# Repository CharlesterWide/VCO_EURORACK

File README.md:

# VCO_EURORACK
Saw core VCO for eurack

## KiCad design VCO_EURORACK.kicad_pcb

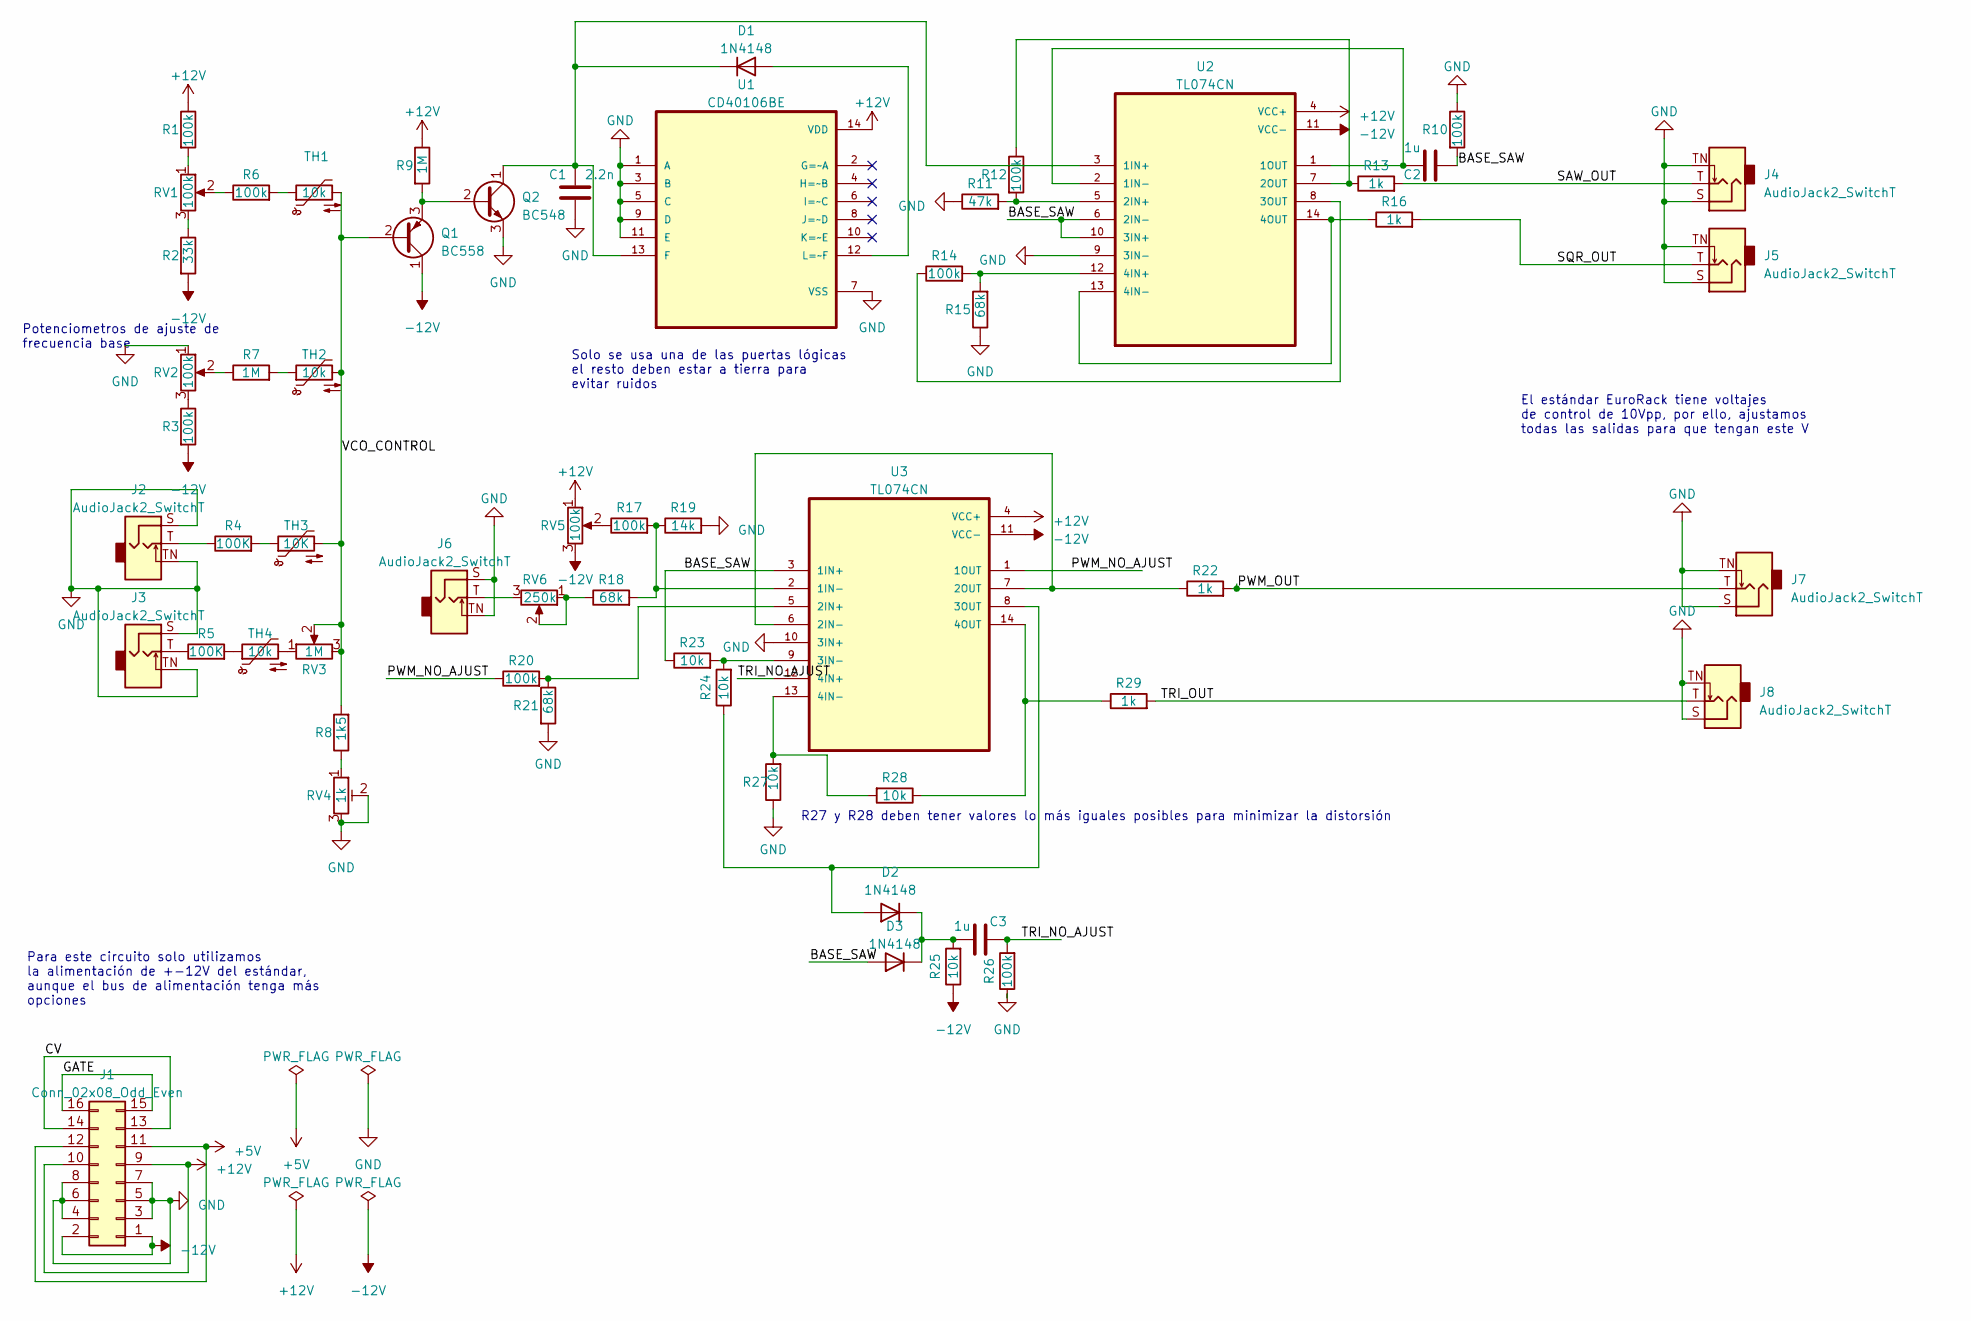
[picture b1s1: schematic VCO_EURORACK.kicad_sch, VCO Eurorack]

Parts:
C1: 2.2n; C_1206_3216Metric_Pad1.33x1.80mm_HandSolder
C2, C3: 1u; C_1206_3216Metric_Pad1.33x1.80mm_HandSolder
D1, D2, D3: 1N4148; D_DO-35_SOD27_P7.62mm_Horizontal
J1: Conn_02x08_Odd_Even; IDC-Header_2x08_P2.54mm_Vertical
J2, J3, J4, J5, J6, J7, J8: AudioJack2_SwitchT; Jack_3.5mm_QingPu_WQP-PJ398SM_Vertical_CircularHoles
Q1: BC558; TO-92_Inline
Q2: BC548; TO-92_Inline
R1, R3, R6, R10, R12, R14, R17, R20, R26: 100k; R_1206_3216Metric_Pad1.30x1.75mm_HandSolder
R2: 33k; R_1206_3216Metric_Pad1.30x1.75mm_HandSolder
R4, R5: 100K; R_1206_3216Metric_Pad1.30x1.75mm_HandSolder
R7, R9: 1M; R_1206_3216Metric_Pad1.30x1.75mm_HandSolder
R8: 1k5; R_1206_3216Metric_Pad1.30x1.75mm_HandSolder
R11: 47k; R_1206_3216Metric_Pad1.30x1.75mm_HandSolder
R13, R16, R22, R29: 1k; R_1206_3216Metric_Pad1.30x1.75mm_HandSolder
R15, R18, R21: 68k; R_1206_3216Metric_Pad1.30x1.75mm_HandSolder
R19: 14k; R_1206_3216Metric_Pad1.30x1.75mm_HandSolder
R23, R24, R25, R27, R28: 10k; R_1206_3216Metric_Pad1.30x1.75mm_HandSolder
RV1, RV2, RV5: 100k; Potentiometer_Omeg_PC16BU_Vertical
RV3: 1M; Potentiometer_Omeg_PC16BU_Vertical
RV4: 1k; Potentiometer_Bourns_3296Y_Vertical
RV6: 250k; Potentiometer_Omeg_PC16BU_Vertical
TH1, TH2, TH4: 10k; R_1206_3216Metric_Pad1.30x1.75mm_HandSolder
TH3: 10K; R_1206_3216Metric_Pad1.30x1.75mm_HandSolder
U1: CD40106BE; DIP794W45P254L1969H508Q14
U2, U3: TL074CN; DIP794W45P254L1969H508Q14

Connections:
+5V: J1.11, J1.12
+12V: J1.9, J1.10, R1.1, R9.1, RV5.1, U1.14 (VDD), U2.4 (VCC+), U3.4 (VCC+)
-12V: J1.1, J1.2, Q1.1 (C), R2.2, R3.2, R25.1, RV5.3, U2.11 (VCC-), U3.11 (VCC-)
/BASE_SAW: C2.2, D3.2 (A), R10.2, R23.1, U2.6 (2IN-), U2.10 (3IN+), U3.3 (1IN+)
/CV: J1.13, J1.14
/GATE: J1.15, J1.16
/PWM_NO_AJUST: R20.1, U3.1 (1OUT)
/PWM_OUT: J7.T, R22.2
/SAW_OUT: J4.T, R13.2
/SQR_OUT: J5.T, R16.2
/TRI_NO_AJUST: C3.2, R26.2, U3.12 (4IN+)
/TRI_OUT: J8.T, R29.2
/VCO_CONTROL: Q1.2 (B), R8.2, RV3.2, RV3.3, TH1.2, TH2.2, TH3.2
GND: C1.2, J1.3, J1.4, J1.5, J1.6, J1.7, J1.8, J2.S, J2.TN, J3.S, J3.TN, J4.S, J4.TN, J5.S, J5.TN, J6.S, J6.TN, J7.S, J7.TN, J8.S, J8.TN, Q2.3 (E), R10.1, R11.1, R15.1, R19.2, R21.2, R26.1, R27.1, RV2.1, RV4.2, RV4.3, U1.1 (A), U1.3 (B), U1.5 (C), U1.7 (VSS), U1.9 (D), U1.11 (E), U2.9 (3IN-), U3.10 (3IN+)
unnamed: D1.2 (A), U1.12 (L=~F)
unnamed: C1.1, D1.1 (K), Q2.1 (C), U1.13 (F), U2.3 (1IN+)
unnamed: D2.2 (A), R24.1, U3.8 (3OUT)
unnamed: C3.1, D2.1 (K), D3.1 (K), R25.2
unnamed: J2.T, R4.1
unnamed: J3.T, R5.1
unnamed: J6.T, RV6.3
unnamed: Q1.3 (E), Q2.2 (B), R9.2
unnamed: R1.2, RV1.1
unnamed: R2.1, RV1.3
unnamed: R3.1, RV2.3
unnamed: R4.2, TH3.1
unnamed: R5.2, TH4.1
unnamed: R6.1, RV1.2
unnamed: R6.2, TH1.1
unnamed: R7.1, RV2.2
unnamed: R7.2, TH2.1
unnamed: R8.1, RV4.1
unnamed: R17.1, RV5.2
unnamed: R18.1, RV6.1, RV6.2
unnamed: RV3.1, TH4.2
unnamed: C2.1, U2.1 (1OUT), U2.2 (1IN-)
unnamed: R11.2, R12.2, U2.5 (2IN+)
unnamed: R12.1, R13.1, U2.7 (2OUT)
unnamed: R14.1, U2.8 (3OUT)
unnamed: R14.2, R15.2, U2.12 (4IN+)
unnamed: R16.1, U2.13 (4IN-), U2.14 (4OUT)
unnamed: R17.2, R18.2, R19.1, U3.2 (1IN-)
unnamed: R20.2, R21.1, U3.5 (2IN+)
unnamed: R22.1, U3.6 (2IN-), U3.7 (2OUT)
unnamed: R23.2, R24.2, U3.9 (3IN-)
unnamed: R27.2, R28.2, U3.13 (4IN-)
unnamed: R28.1, R29.1, U3.14 (4OUT)

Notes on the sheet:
Para este circuito solo utilizamos la alimentación de +-12V del estándar, aunque el bus de alimentación tenga más opciones
R27 y R28 deben tener valores lo más iguales posibles para minimizar la distorsión
El estándar EuroRack tiene voltajes de control de 10Vpp, por ello, ajustamos todas las salidas para que tengan este V
Potenciometros de ajuste de frecuencia base
Solo se usa una de las puertas lógicas el resto deben estar a tierra para evitar ruidos

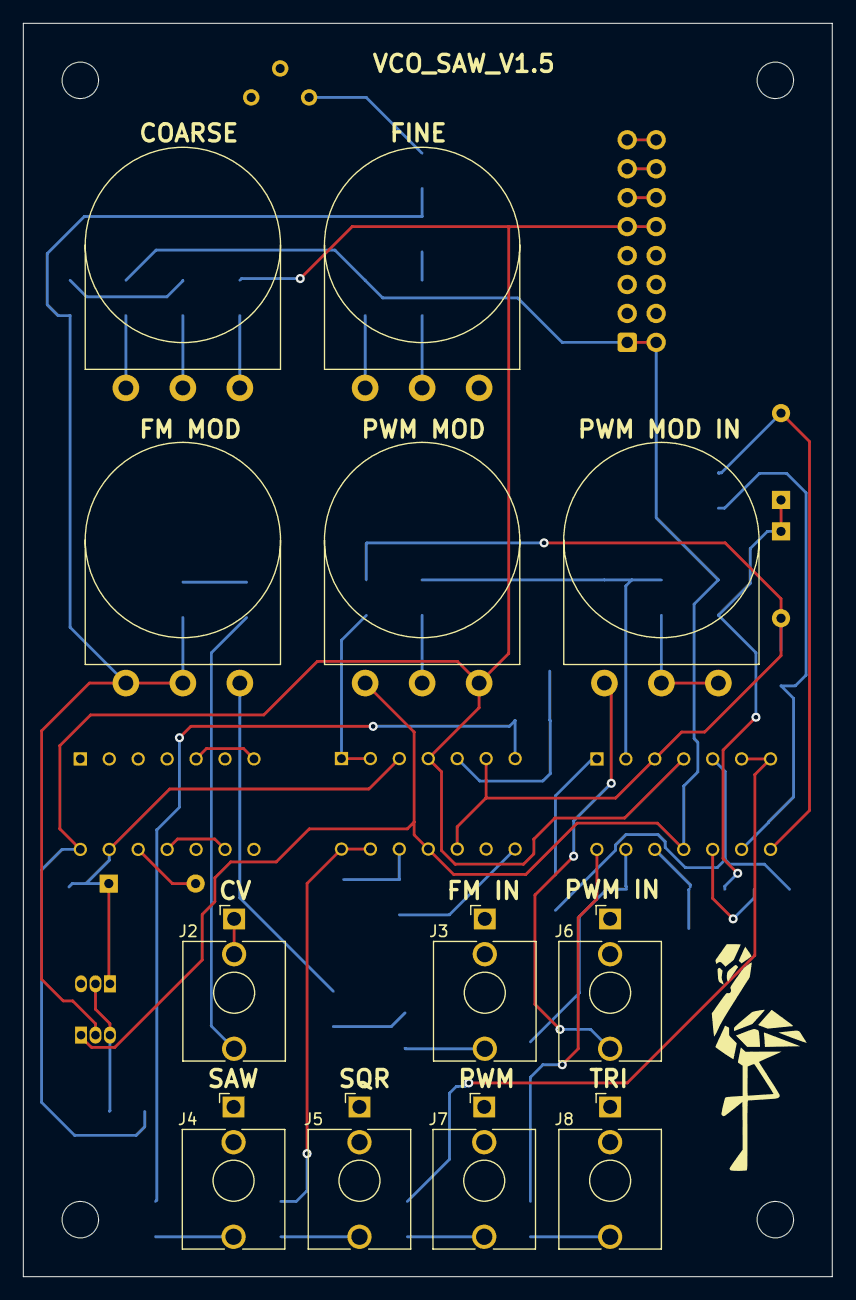
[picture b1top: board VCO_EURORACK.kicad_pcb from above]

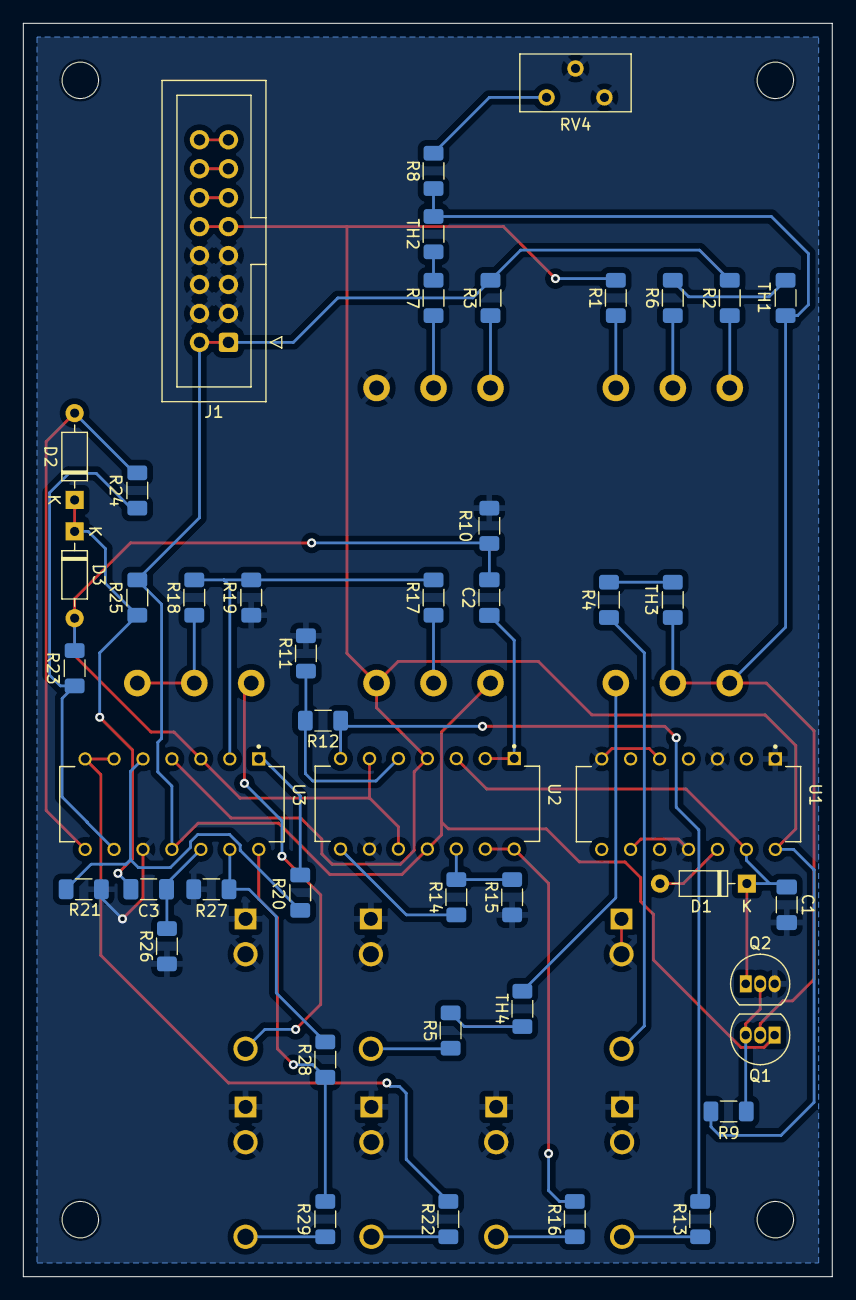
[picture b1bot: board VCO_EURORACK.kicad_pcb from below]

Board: 2 copper layers, 71.0 x 110.0 mm, 58 parts (46 on the bottom side), 47 nets.

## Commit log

2023-08-07 Initial files upload
